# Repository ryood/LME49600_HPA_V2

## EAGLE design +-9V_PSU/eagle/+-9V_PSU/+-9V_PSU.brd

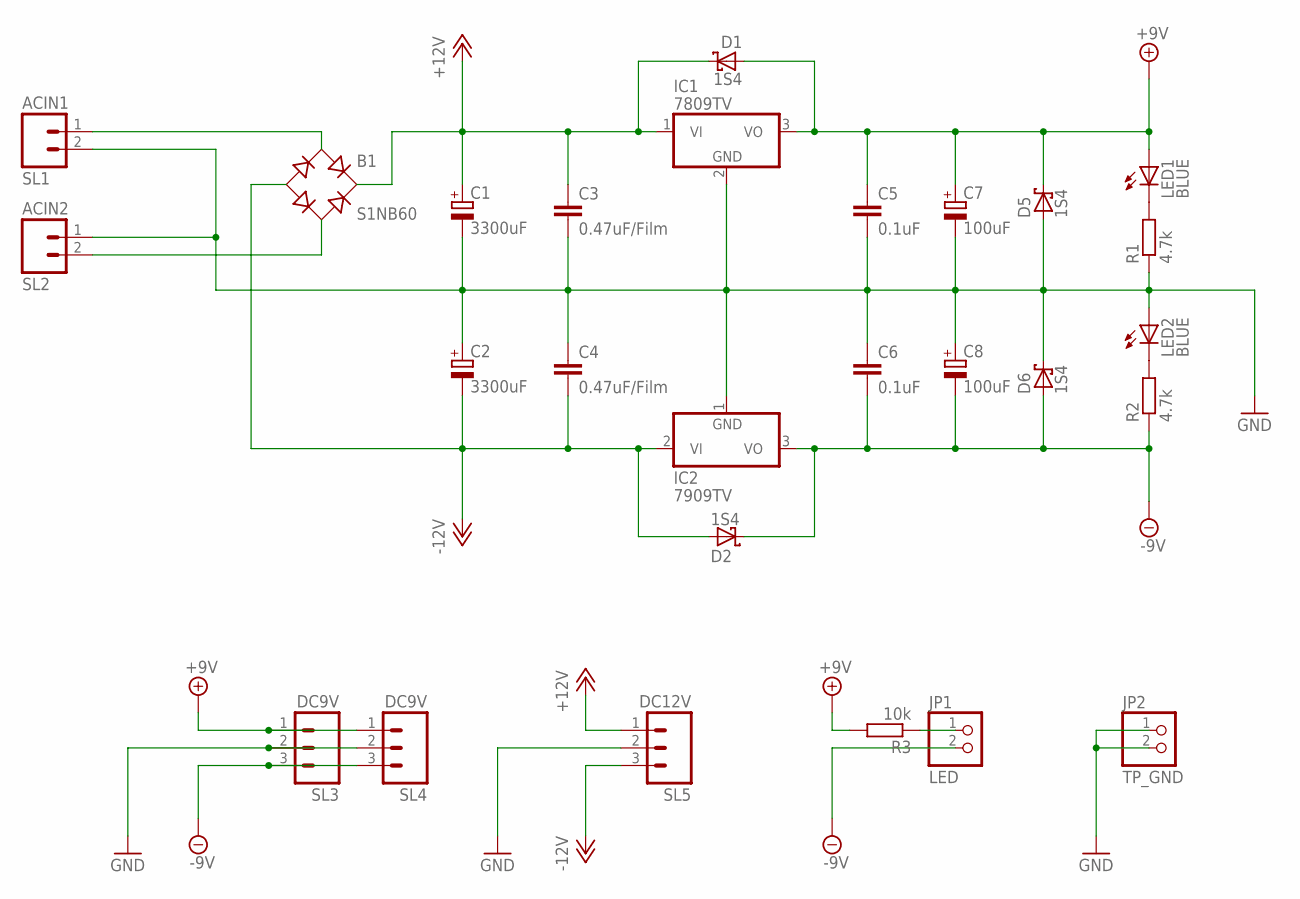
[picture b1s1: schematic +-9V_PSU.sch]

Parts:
B1: S1NB60; B-DIL
C1, C2: 3300uF; EB25D
C3, C4: 0.47uF/Film; C050-045X075
C5, C6: 0.1uF; C025-024X044
C7, C8: 100uF; SANYO-OSCON_C6
D1, D2, D5, D6: 1S4; DO35-7
IC1: 7809TV; TO220V
IC2: 7909TV; TO220V
JP1: LED; 1X02
JP2: TP_GND; 1X02
LED1, LED2: BLUE; LED3MM
R1, R2: 4.7k; 0207/7
R3: 10k; 0207/7
SL1: ACIN1; 02P
SL2: ACIN2; 02P
SL3, SL4: DC9V; 03P
SL5: DC12V; 03P

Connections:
+9V: C5.1, C7.+, D1.A, D5.C, IC1.3 (VO), LED1.A, R3.2, SL3.1, SL4.1
+12V: B1.+, C1.+, C3.1, D1.C, IC1.1 (VI), SL5.1
-9V: C6.2, C8.-, D2.C, D6.A, IC2.3 (VO), JP1.2, R2.1, SL3.3, SL4.3
-12V: B1.-, C2.-, C4.2, D2.A, IC2.2 (VI), SL5.3
GND: C1.-, C2.+, C3.2, C4.1, C5.2, C6.1, C7.-, C8.+, D5.A, D6.C, IC1.2 (GND), IC2.1 (GND), JP2.1, JP2.2, LED2.A, R1.1, SL1.2, SL2.1, SL3.2, SL4.2, SL5.2
unnamed: LED2.K (C), R2.2
unnamed: JP1.1, R3.1
unnamed: LED1.K (C), R1.2
unnamed: B1.AC1, SL1.1
unnamed: B1.AC2, SL2.2

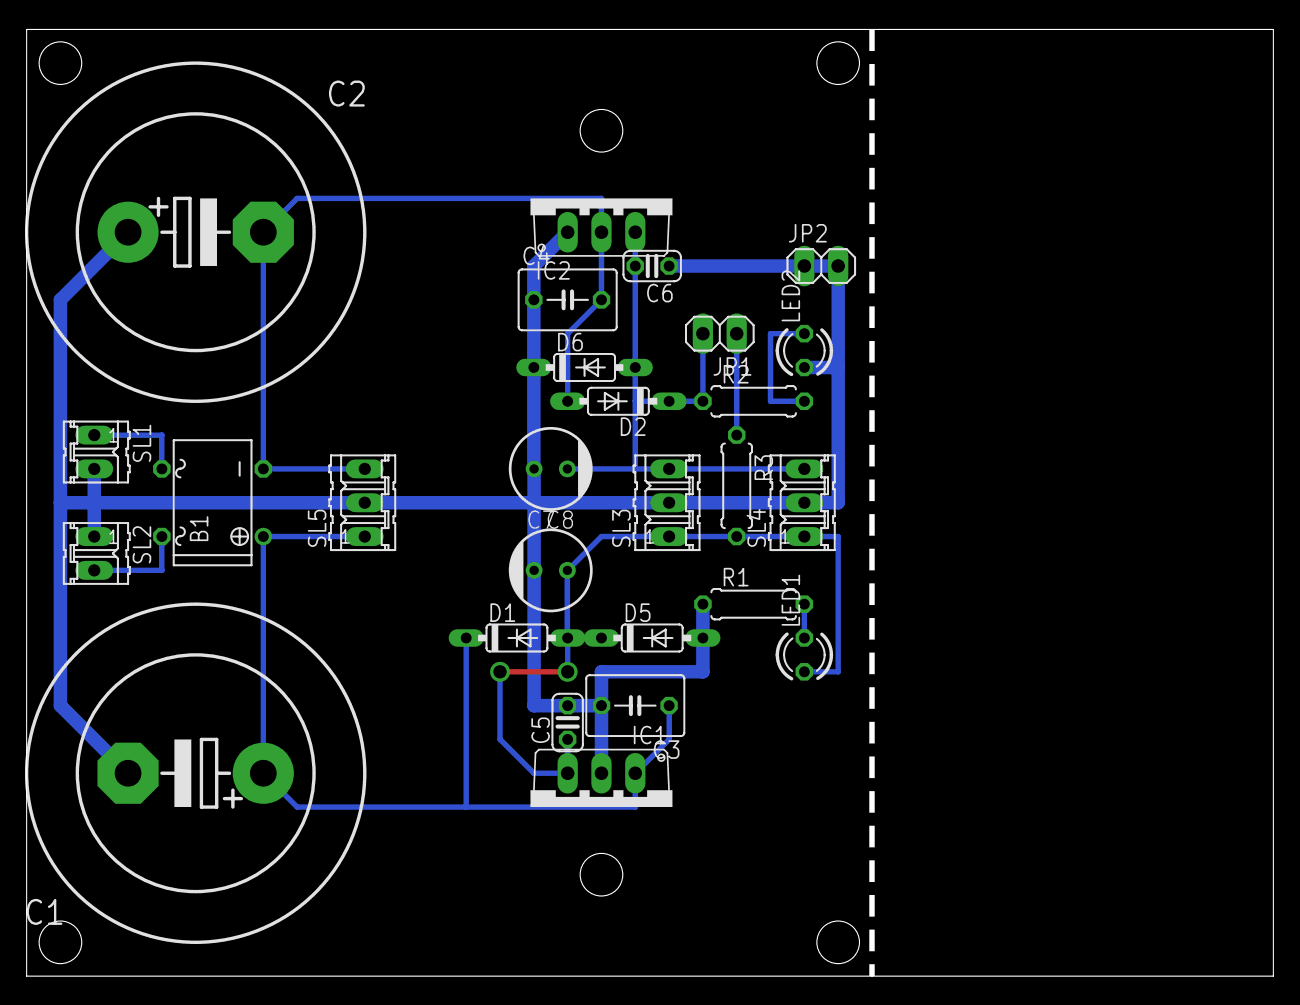
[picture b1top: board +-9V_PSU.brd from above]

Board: 2 copper layers, 93.2 x 71.1 mm, 27 parts (0 on the bottom side), 10 nets.

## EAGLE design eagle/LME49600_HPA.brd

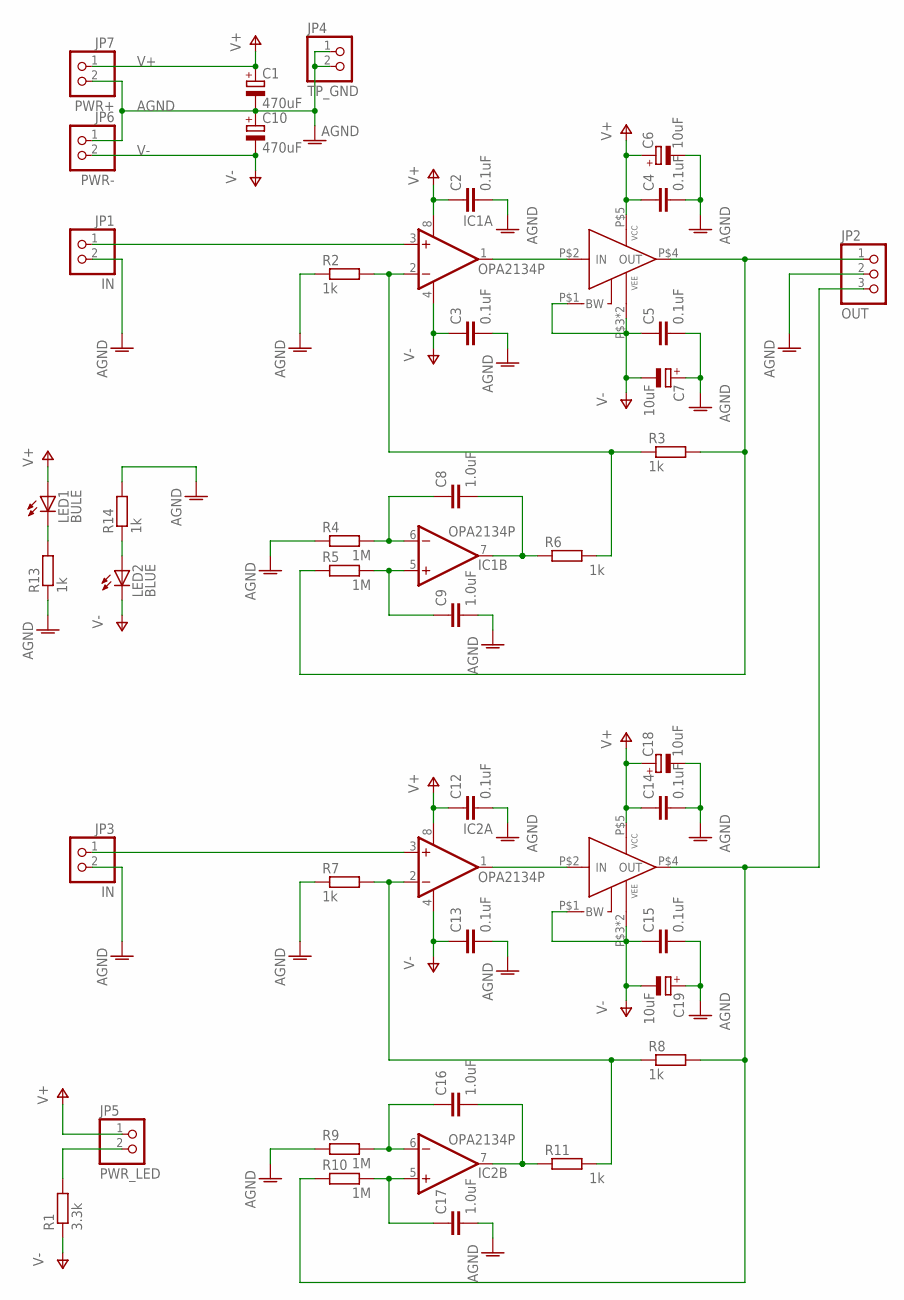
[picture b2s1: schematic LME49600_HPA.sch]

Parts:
C1, C10: 470uF; E7,5-16
C2, C3, C4, C5, C12, C13, C14, C15: 0.1uF; C025-024X044
C6, C7, C18, C19: 10uF; E2,5-5
C8, C9, C16, C17: 1.0uF; C050-050X075
IC1, IC2: OPA2134P; DIL08
JP1, JP3: IN; 1X02
JP2: OUT; 1X03
JP4: TP_GND; 1X02
JP5: PWR_LED; 1X02
JP6: PWR-; 1X02
JP7: PWR+; 1X02
LED1: BULE; LED3MM
LED2: BLUE; LED3MM
R1: 3.3k; 0207/7
R2, R3, R6, R7, R8, R11, R13, R14: 1k; 0207/7
R4, R5, R9, R10: 1M; 0207/7
U$1, U$2: LME49600-BRD3; TO-263-5L

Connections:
AGND: C1.-, C2.2, C3.2, C4.2, C5.2, C6.-, C7.+, C9.2, C10.+, C12.2, C13.2, C14.2, C15.2, C17.2, C18.-, C19.+, JP1.2, JP2.2, JP3.2, JP4.1, JP4.2, JP6.1, JP7.2, R2.1, R4.1, R7.1, R9.1, R13.1, R14.2
unnamed: IC1.3 (+IN), JP1.1
unnamed: LED2.A, R14.1
unnamed: IC1.2 (-IN), R2.2, R3.1, R6.2
unnamed: IC2.2 (-IN), R7.2, R8.1, R11.2
unnamed: IC2.1 (OUT), U$2.P$2 (IN)
unnamed: C8.1, IC1.6 (-IN), R4.2
unnamed: IC1.1 (OUT), U$1.P$2 (IN)
unnamed: C9.1, IC1.5 (+IN), R5.2
unnamed: C16.1, IC2.6 (-IN), R9.2
unnamed: C17.1, IC2.5 (+IN), R10.2
unnamed: C8.2, IC1.7 (OUT), R6.1
unnamed: C16.2, IC2.7 (OUT), R11.1
unnamed: JP2.3, R8.2, R10.1, U$2.P$4 (OUT)
unnamed: JP2.1, R3.2, R5.1, U$1.P$4 (OUT)
unnamed: IC2.3 (+IN), JP3.1
unnamed: JP5.2, R1.2
unnamed: LED1.K (C), R13.2
V+: C1.+, C2.1, C4.1, C6.+, C12.1, C14.1, C18.+, IC1.8 (V+), IC2.8 (V+), JP5.1, JP7.1, LED1.A, U$1.P$5 (VCC), U$2.P$5 (VCC)
V-: C3.1, C5.1, C7.-, C10.-, C13.1, C15.1, C19.-, IC1.4 (V-), IC2.4 (V-), JP6.2, LED2.K (C), R1.1, U$1.P$1 (BW), U$1.P$3 (VEE), U$1.P$6 (VEE), U$2.P$1 (BW), U$2.P$3 (VEE), U$2.P$6 (VEE)

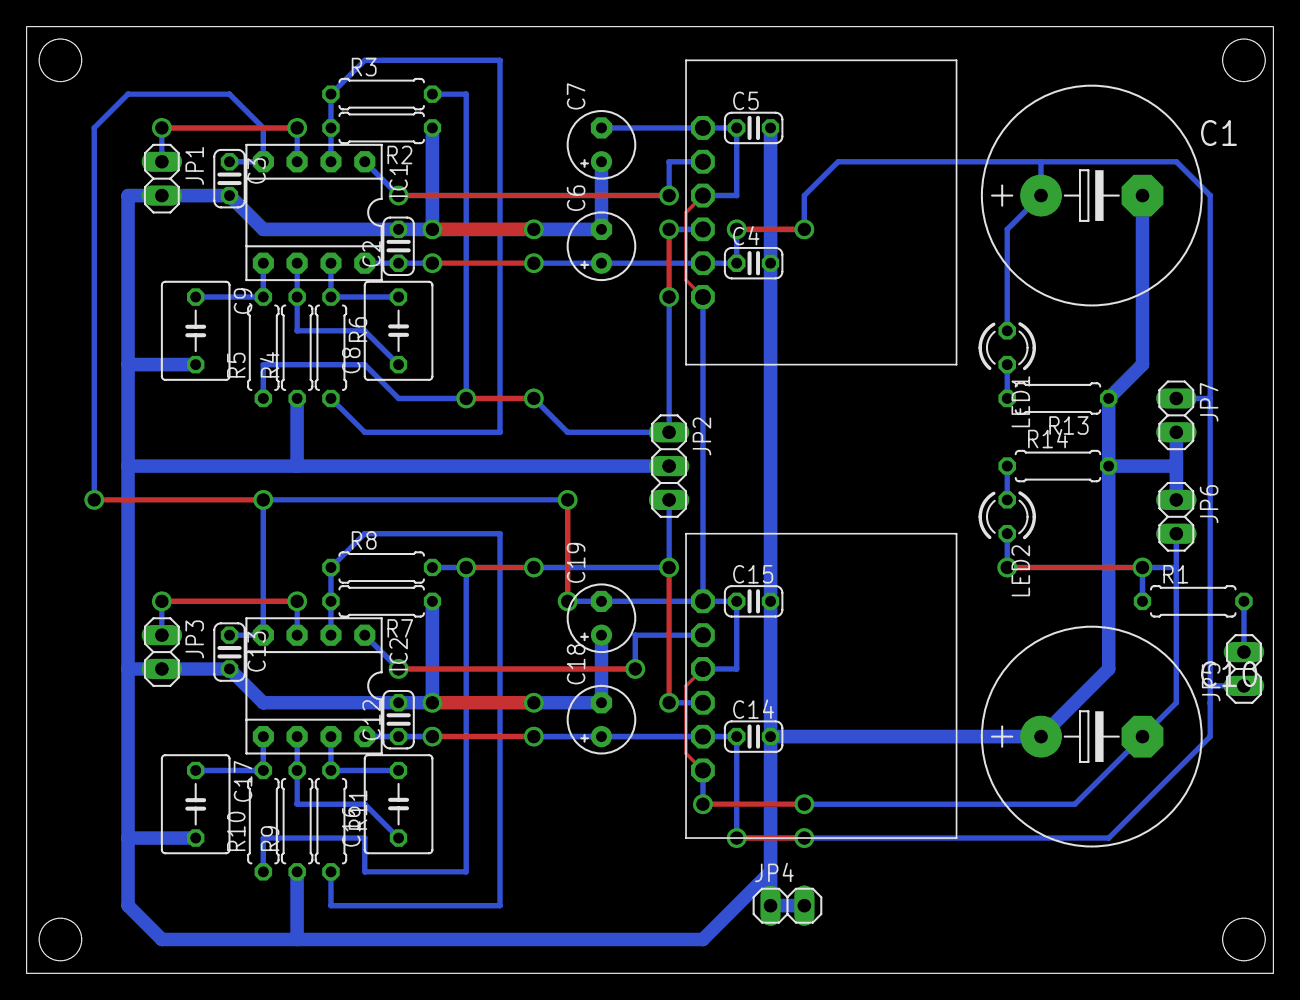
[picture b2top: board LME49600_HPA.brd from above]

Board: 2 copper layers, 93.7 x 71.1 mm, 44 parts (0 on the bottom side), 20 nets.

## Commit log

2017-01-30 Update: the board design (tantal->Alminium)
2017-02-02 Update: Eagle files
2017-02-08 Updated: テスト表
2017-02-08 Eagle Files: Add TP-GND
2017-02-08 Add: Pictures
2017-02-24 Add: PWR LED
2017-03-01 Add image files
2017-03-10 Add: +-9V_PSU
2017-03-10 +-9V PSU Board design
2017-03-10 +-9V_PSU Update
2017-03-10 Schematic & Board Image
2017-03-21 Add: +/-9V PSU Case
2017-03-24 Update: Case designe
